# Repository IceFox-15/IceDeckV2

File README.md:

# IceDeckV2

## Inspiration
I was inspirated by the Streamdeck and decided to make my own, adjusted to my purposes. I first thought about what buttons I would need and then started sketching. I added 2 buttons for Discord, I also wanted to control my music so I added Play/Pause and Skip buttons and also some for brightness. Then I also added a screen for the time or gifs/memes and a volumeknob. Also my README is based on the layout of Ducc's Fidget Toy by Dongathan-Jong.

## Challanges
It was hard to find the go with KiCad, bc I was using it for the first time. It was especially difficult to find a scheme and footprint of the screen module, I ended up making my own. The easiest thing was the CAD part, because I was already using it for a long time. I did it on Onshape and added all the parts to see how it would look, if there is a missing CAD file, pls msg me. Coding, was js coding...

## Specifications

BOM:
- 9x Cherry MX switches
- 12x Blank DSA keycaps (3x for spare)
- 1x XIAO-RP2040
- 1x EC11 Rotary encoder
- 1x 0.91 inch OLED display

Pictures:
Schematic            |  PCB         |   Case
:-------------------------:|:-------------------------:|:-------------------------:|
    |    | 

Others:
- Firmware runs on KMK

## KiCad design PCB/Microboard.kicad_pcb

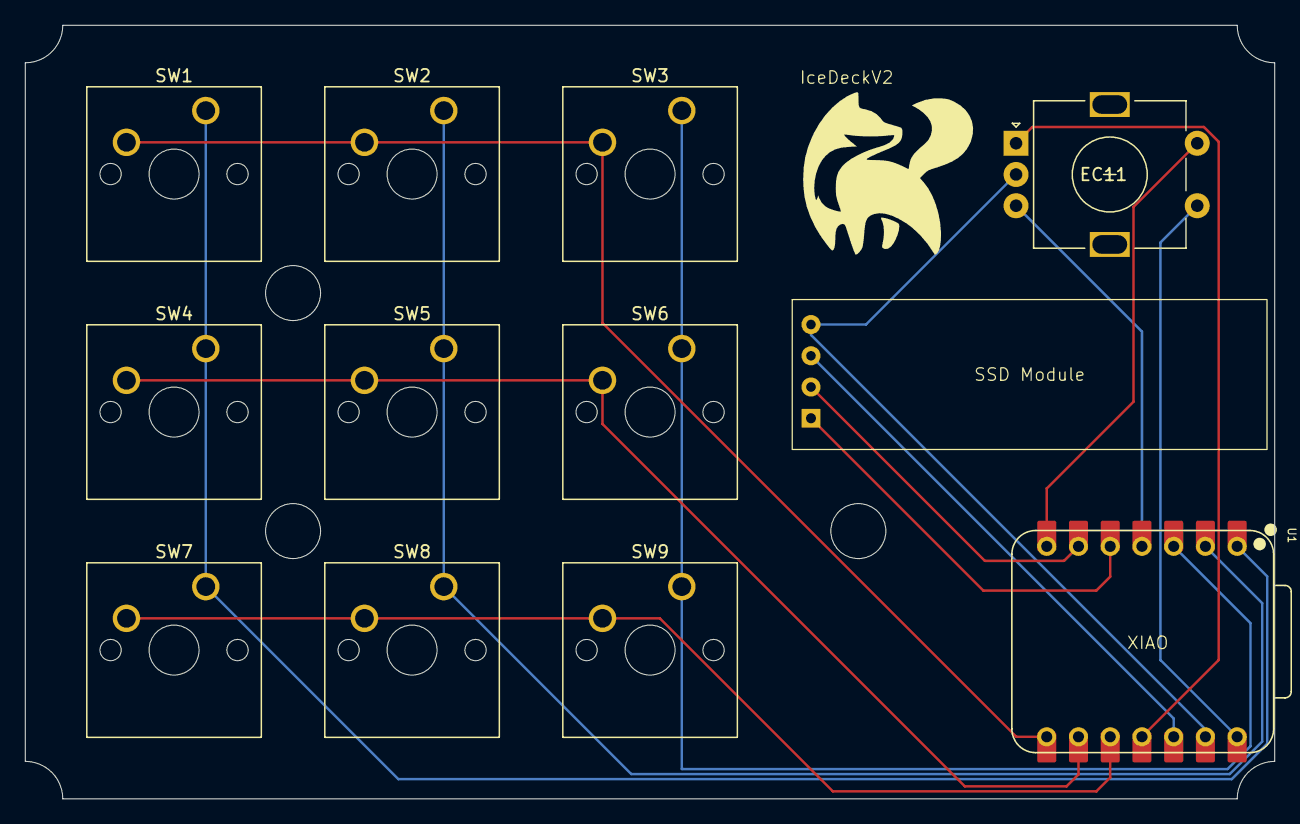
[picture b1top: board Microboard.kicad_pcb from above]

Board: 2 copper layers, 100.0 x 61.9 mm, 12 parts (0 on the bottom side), 14 nets.

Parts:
EC11: RotaryEncoder_Switch; RotaryEncoder_Alps_EC11E-Switch_Vertical_H20mm
SSD Module: ssd128x32 module
SW1, SW2, SW3, SW4, SW5, SW6, SW7, SW8, SW9: SW_Push; SW_Cherry_MX_1.00u_PCB
U1: XIAO-RP2040-DIP

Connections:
+5V: EC11.S1, U1.14 (VBUS)
COL1: SW1.2, SW2.2, SW3.2, U1.8 (GPIO1/RX)
COL2: SW4.2, SW5.2, SW6.2, U1.9 (GPIO2/SCK)
COL3: SW7.2, SW8.2, SW9.2, U1.10 (GPIO4/MISO)
D_SCL: SSD Module.3 (SCL), U1.6 (GPIO7/SCL)
D_SDA: SSD Module.4 (SDA), U1.5 (GPIO6/SDA)
D_VCC: SSD Module.2 (VCC), U1.12 (3V3)
ENC_A: EC11.A, U1.11 (GPIO3/MOSI)
ENC_B: EC11.B, U1.4 (GPIO29/ADC3/A3)
ENC_S2: EC11.S2, U1.7 (GPIO0/TX)
GND: EC11.C, SSD Module.1 (GND), U1.13 (GND)
ROW1: SW1.1, SW4.1, SW7.1, U1.1 (GPIO26/ADC0/A0)
ROW2: SW2.1, SW5.1, SW8.1, U1.2 (GPIO27/ADC1/A1)
ROW3: SW3.1, SW6.1, SW9.1, U1.3 (GPIO28/ADC2/A2)

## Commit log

2025-12-06 Update README to clarify firmware information
2025-12-06 Create CAD
2025-12-06 Create Temp
2025-12-06 Rename BottomCase.step to CAD/BottomCase.step
2025-12-06 Rename IceDeckAssembeld.step to CAD/IceDeckAssembeld.step
2025-12-06 Rename IceDeckPCB.step to CAD/IceDeckPCB.step
2025-12-06 Rename TopCase.step to CAD/TopCase.step
2025-12-06 Update and rename temp to README
